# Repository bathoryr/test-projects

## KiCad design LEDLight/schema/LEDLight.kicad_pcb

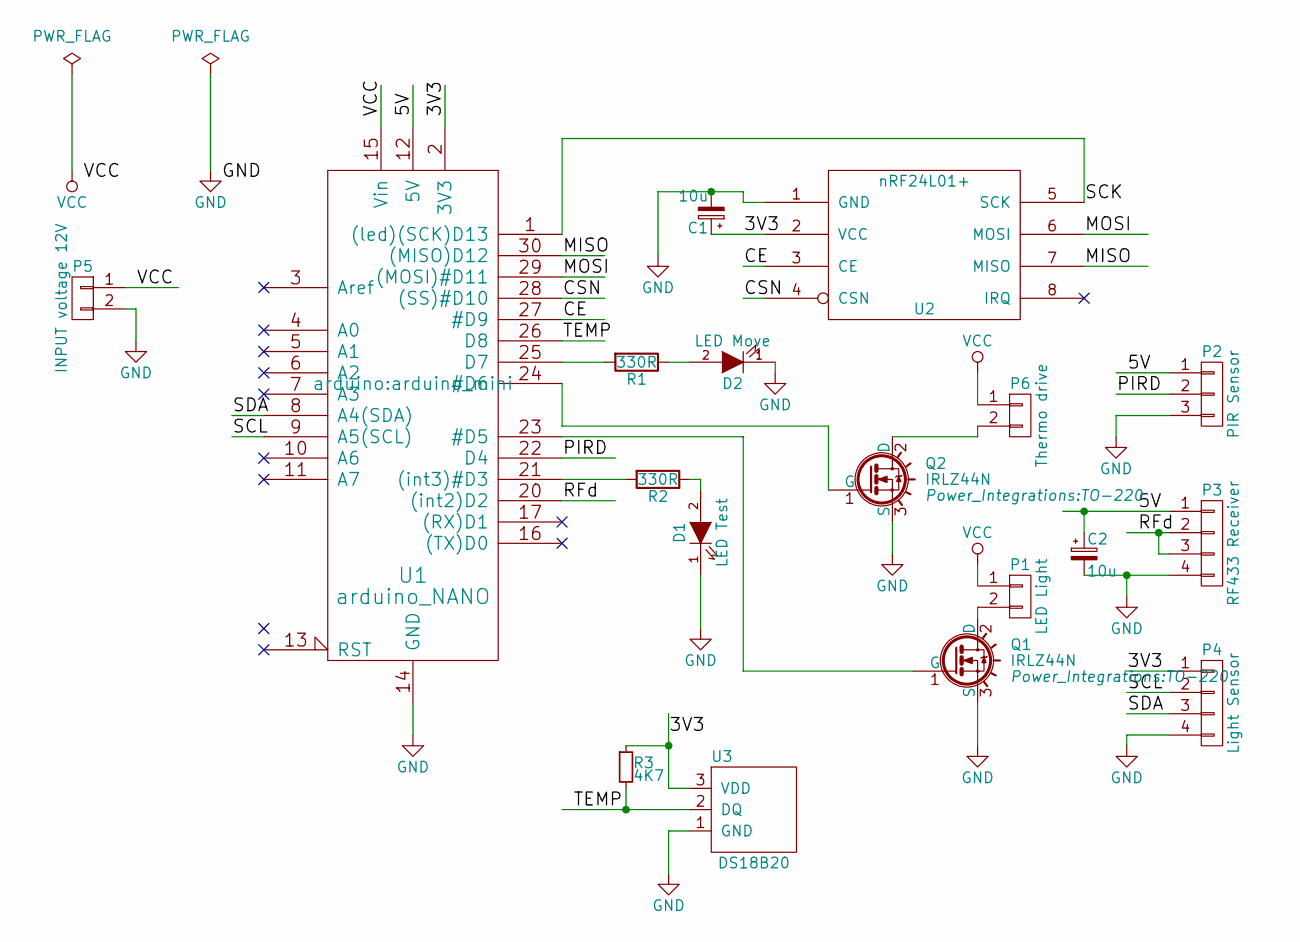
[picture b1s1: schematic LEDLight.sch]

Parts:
C1, C2: 10u; C_Radial_D5_L11_P2.5
D1: LED Test; LED-3MM
D2: LED Move; LED-3MM
P1: LED Light; Pin_Header_Straight_1x02_Pitch3.96mm_Friction_Lock
P2: PIR Sensor; Pin_Header_Straight_1x03
P3: RF433 Receiver; Pin_Header_Straight_1x04
P4: Light Sensor; Pin_Header_Straight_1x04
P5: INPUT voltage 12V; Pin_Header_Straight_1x02_Pitch3.96mm_Friction_Lock
P6: Thermo drive; Pin_Header_Straight_1x02_Pitch3.96mm_Friction_Lock
Q1, Q2: IRLZ44N; TO-220
R1: 330R; Resistor_Vertical_RM5mm
R2: 330R; Resistor_Horizontal_RM10mm
R3: 4K7; Resistor_Vertical_RM5mm
U1: arduino_NANO; arduino_mini
U2: nRF24L01+; NRF24L01
U3: DS18B20; TO-92_Inline_Narrow_Oval

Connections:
/3V3: C1.1, P4.1, R3.1, U1.2 (3V3), U2.2 (VCC), U3.3 (VDD)
/5V: C2.1, P2.1, P3.1, U1.12 (5V)
/CE: U1.27 (#D9), U2.3 (CE)
/CSN: U1.28 ((SS)#D10), U2.4 (CSN)
/MISO: U1.30 ((MISO)D12), U2.7 (MISO)
/MOSI: U1.29 ((MOSI)#D11), U2.6 (MOSI)
/PIRD: P2.2, U1.22 (D4)
/RFd: P3.2, P3.3, U1.20 ((int2)D2)
/SCK: U1.1 ((led)(SCK)D13), U2.5 (SCK)
/SCL: P4.2, U1.9 (A5(SCL))
/SDA: P4.3, U1.8 (A4(SDA))
/TEMP: R3.2, U1.26 (D8), U3.2 (DQ)
GND: C1.2, C2.2, D1.1 (K), D2.1 (K), P2.3, P3.4, P4.4, P5.2, Q1.3 (S), Q2.3 (S), U1.14 (GND), U1.19 (GND), U2.1 (GND), U3.1 (GND)
unnamed: D1.2 (A), R2.1
unnamed: D2.2 (A), R1.1
unnamed: P1.2, Q1.2 (D)
unnamed: P6.2, Q2.2 (D)
unnamed: Q1.1 (G), U1.23 (#D5)
unnamed: Q2.1 (G), U1.24 (#D6)
unnamed: R1.2, U1.25 (D7)
unnamed: R2.2, U1.21 ((int3)#D3)
VCC: P1.1, P5.1, P6.1, U1.15 (Vin)

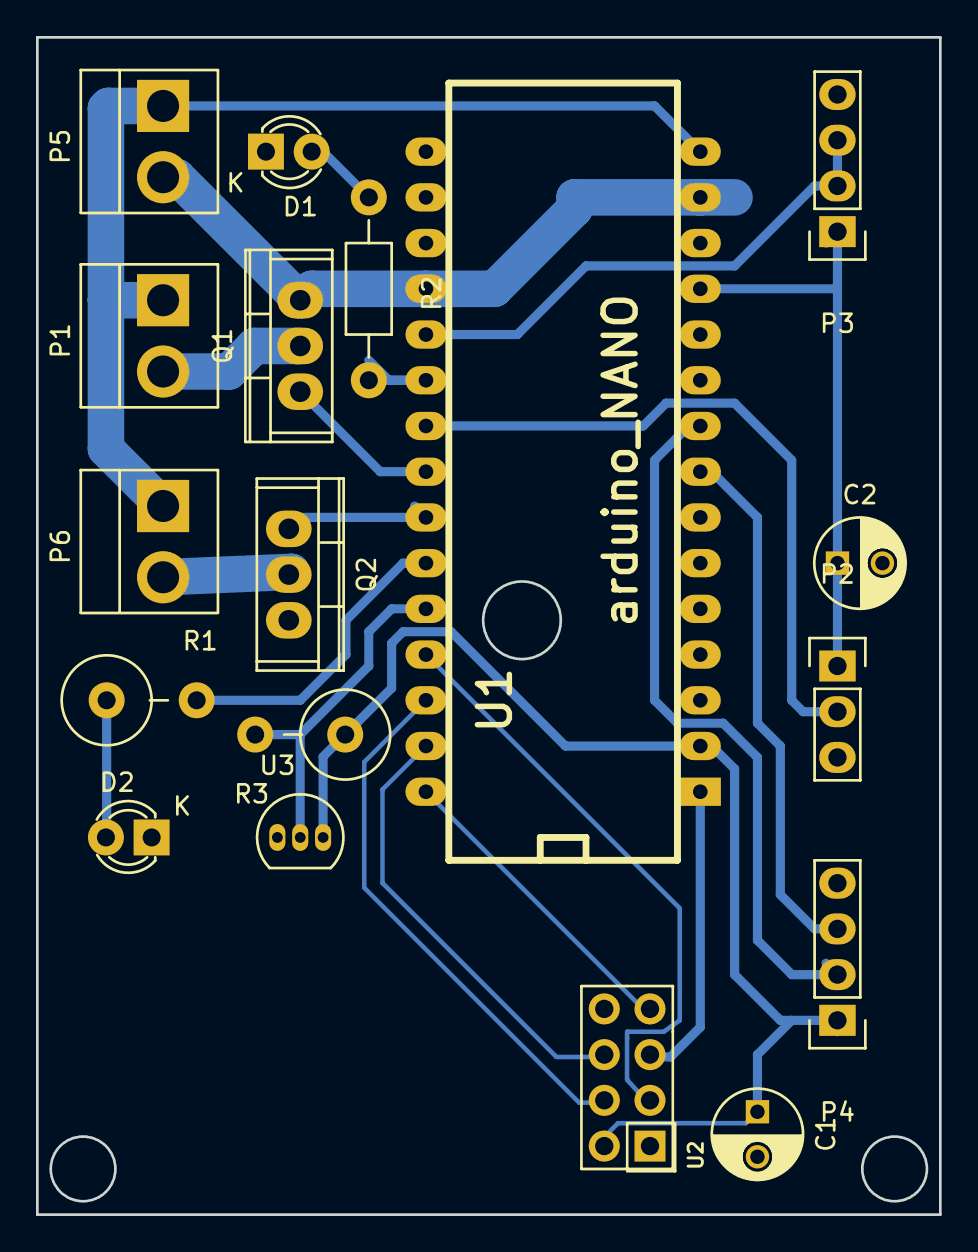
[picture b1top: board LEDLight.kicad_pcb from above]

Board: 2 copper layers, 50.2 x 65.4 mm, 18 parts (0 on the bottom side), 22 nets.

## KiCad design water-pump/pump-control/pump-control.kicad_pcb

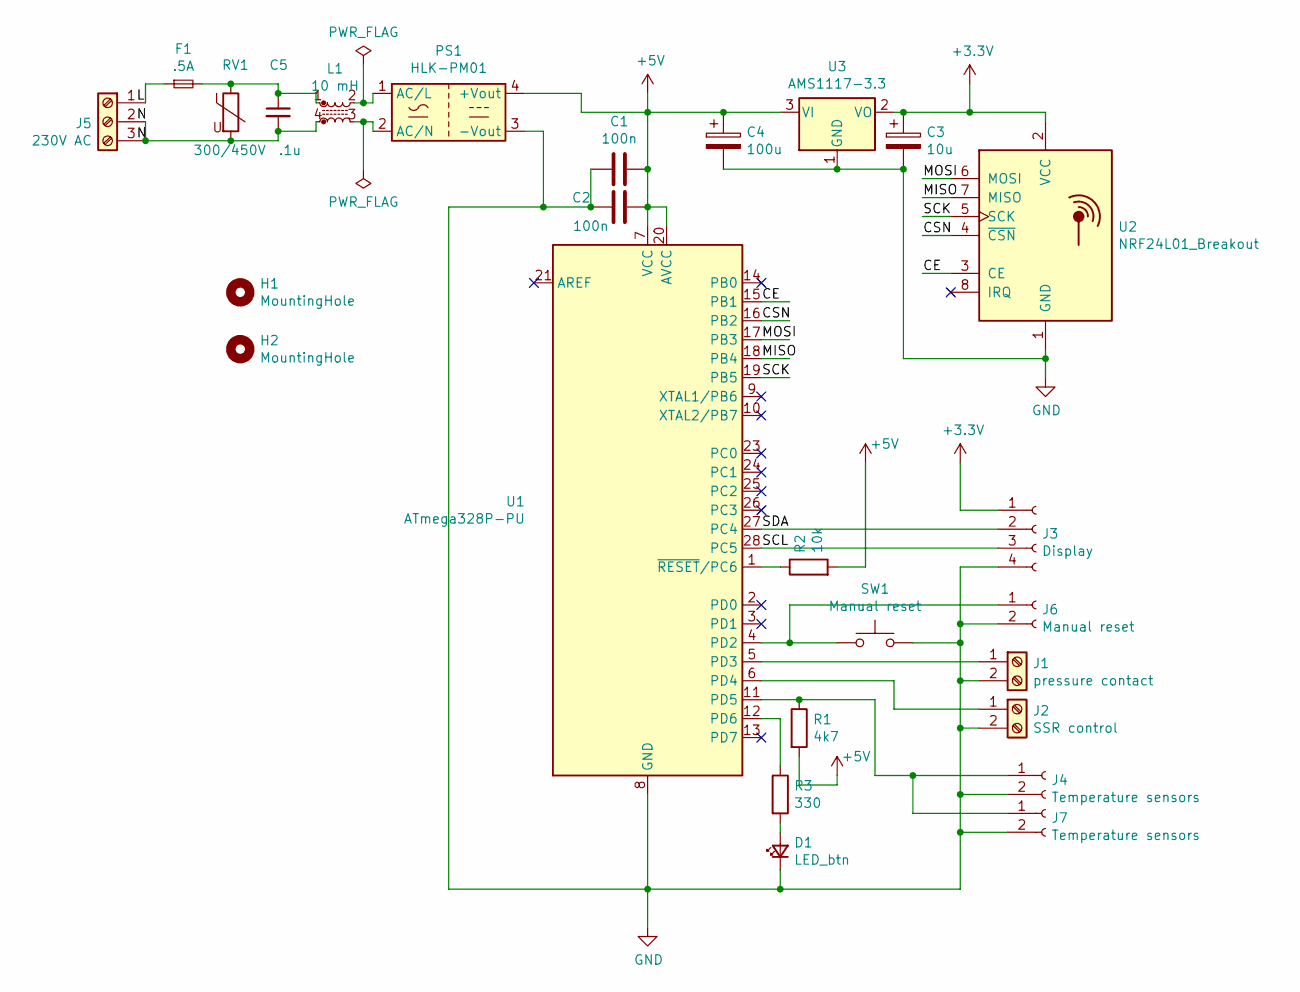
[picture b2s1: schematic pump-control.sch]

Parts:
C1, C2: 100n; C_Disc_D7.5mm_W4.4mm_P5.00mm
C3: 10u; CP_Radial_D7.5mm_P2.50mm
C4: 100u; CP_Radial_D7.5mm_P2.50mm
C5: .1u; C_Rect_L18.0mm_W6.0mm_P15.00mm_FKS3_FKP3
D1: LED_btn; PinHeader_1x02_P2.54mm_Vertical
F1: .5A; Fuseholder_TR5_Littelfuse_No560_No460
H1, H2: MountingHole; MountingHole_3.2mm_M3
J1: pressure contact; TerminalBlock_Phoenix_MKDS-1,5-2-5.08_1x02_P5.08mm_Horizont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
J2: SSR control; TerminalBlock_Phoenix_MKDS-1,5-2-5.08_1x02_P5.08mm_Horizont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
J3: Display; PinSocket_1x04_P2.54mm_Vertical
J4, J7: Temperature sensors; PinSocket_1x02_P2.54mm_Vertical
J5: 230V AC; TerminalBlock_Phoenix_MKDS-1,5-3-5.08_1x03_P5.08mm_Horizont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
J6: Manual reset; PinSocket_1x02_P2.54mm_Vertical
L1: 10 mH; L_CommonMode_Wuerth_WE-CMB-XS
PS1: HLK-PM01; Converter_ACDC_HiLink_HLK-PMxx
R1: 4k7; R_Axial_DIN0207_L6.3mm_D2.5mm_P10.16mm_Horizontal
R2: 10k; R_Axial_DIN0207_L6.3mm_D2.5mm_P10.16mm_Horizontal
R3: 330; R_Axial_DIN0207_L6.3mm_D2.5mm_P10.16mm_Horizontal
RV1: 300/450V; RV_Disc_D12mm_W3.9mm_P7.5mm
SW1: Manual reset; SW_PUSH_6mm
U1: ATmega328P-PU; DIP-28_W7.62mm
U2: NRF24L01_Breakout; nRF24L01_Breakout
U3: AMS1117-3.3; SOT-223-3_TabPin2

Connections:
+3V3: C3.1, J3.1, U2.2 (VCC), U3.2 (VO)
+5V: C1.1, C2.1, C4.1, PS1.4 (+Vout), R1.2, R2.2, U1.7 (VCC), U1.20 (AVCC), U3.3 (VI)
/CE: U1.15 (PB1), U2.3 (CE)
/CSN: U1.16 (PB2), U2.4 (~CSN)
/MISO: U1.18 (PB4), U2.7 (MISO)
/MOSI: U1.17 (PB3), U2.6 (MOSI)
/SCK: U1.19 (PB5), U2.5 (SCK)
/SCL: J3.3, U1.28 (PC5)
/SDA: J3.2, U1.27 (PC4)
GND: C1.2, C2.2, C3.2, C4.2, D1.1 (K), J1.2, J2.2, J3.4, J4.2, J6.2, J7.2, PS1.3 (-Vout), SW1.2, U1.8 (GND), U1.22 (GND), U2.1 (GND), U3.1 (GND)
unnamed: C5.1, F1.2, L1.1, RV1.1
unnamed: C5.2, J5.2, J5.3, L1.4, RV1.2
unnamed: D1.2 (A), R3.2
unnamed: F1.1, J5.1
unnamed: J1.1, U1.5 (PD3)
unnamed: J2.1, U1.6 (PD4)
unnamed: J4.1, J7.1, R1.1, U1.11 (PD5)
unnamed: J6.1, SW1.1, U1.4 (PD2)
unnamed: L1.2, PS1.1 (AC/L)
unnamed: L1.3, PS1.2 (AC/N)
unnamed: R2.1, U1.1 (~RESET~/PC6)
unnamed: R3.1, U1.12 (PD6)

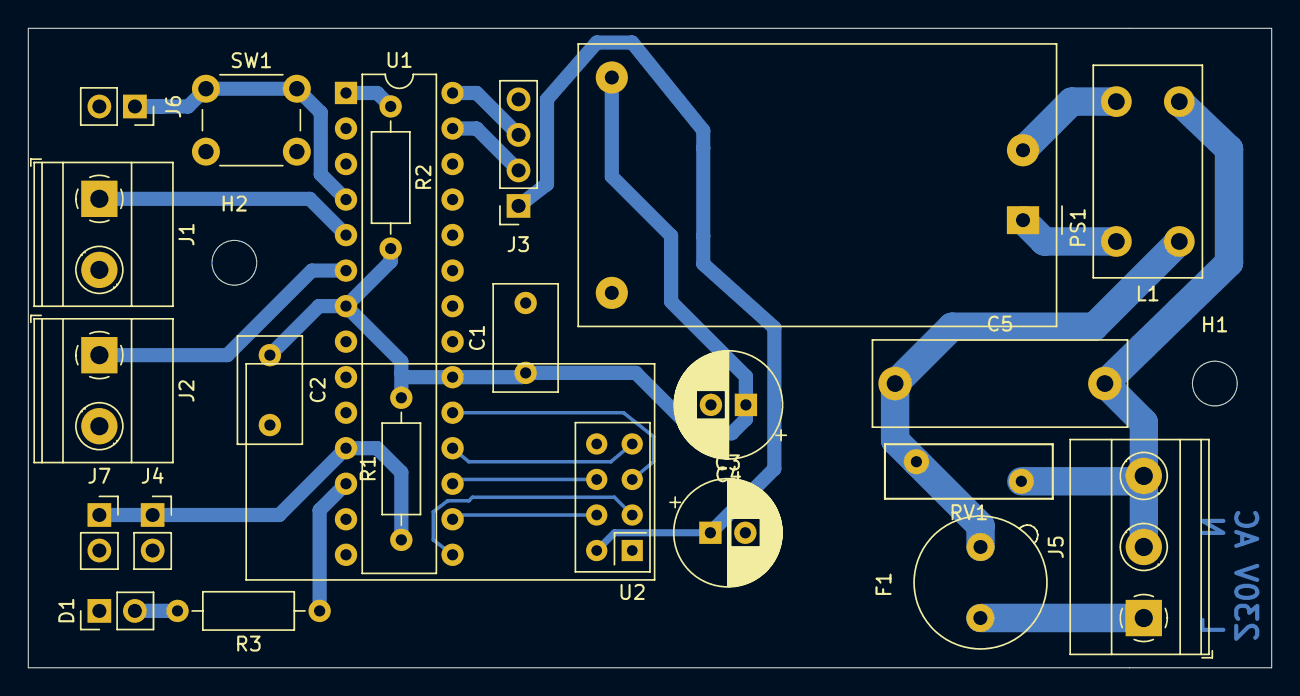
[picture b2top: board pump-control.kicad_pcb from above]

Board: 2 copper layers, 88.9 x 45.7 mm, 26 parts (1 on the bottom side), 22 nets.

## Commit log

2020-10-25 Initial push
2020-10-26 Added pump control class
2020-10-28 Runtime check
2020-10-28 First working prototype
2020-10-29 Confirmation button logic changed
2020-10-30 Cleanup the code, remove Serial
2020-10-31 Basic MySensors functions
2020-11-01 Send status to MySensors. Finished prototype
2020-11-06 Hotfix for confirm button press event
2020-11-06 Fix string format storage
2020-11-06 Added kicad project
2020-11-12 Changed button handler, interval for sending messages
2020-11-14 Components reorganization
2020-11-17 Schema + PCB
2020-11-22 Added new projects
2020-11-22 Minor fixes
2020-12-24 Chnages in status notification
2020-12-28 Fixed input inductor pinout
2020-12-29 Adding LED control class
2020-12-29 Added control of button LED
2021-01-01 added ki-cad projects
2021-02-21 Add doorbell control
2021-04-01 Added another button
2021-04-01 Start without GW, enable stop button in RUN state
2021-04-09 Send heartbeat
2021-04-09 Minor changes in parameters
2021-04-09 Added RPiGuard to the workspace
2021-04-10 Changed min. Volt
2021-04-10 Updated comment
2021-05-02 RF scanner for NRF modules
2021-05-02 CelluBtton refactoring to handle long click
2022-01-16 LEDlight update
